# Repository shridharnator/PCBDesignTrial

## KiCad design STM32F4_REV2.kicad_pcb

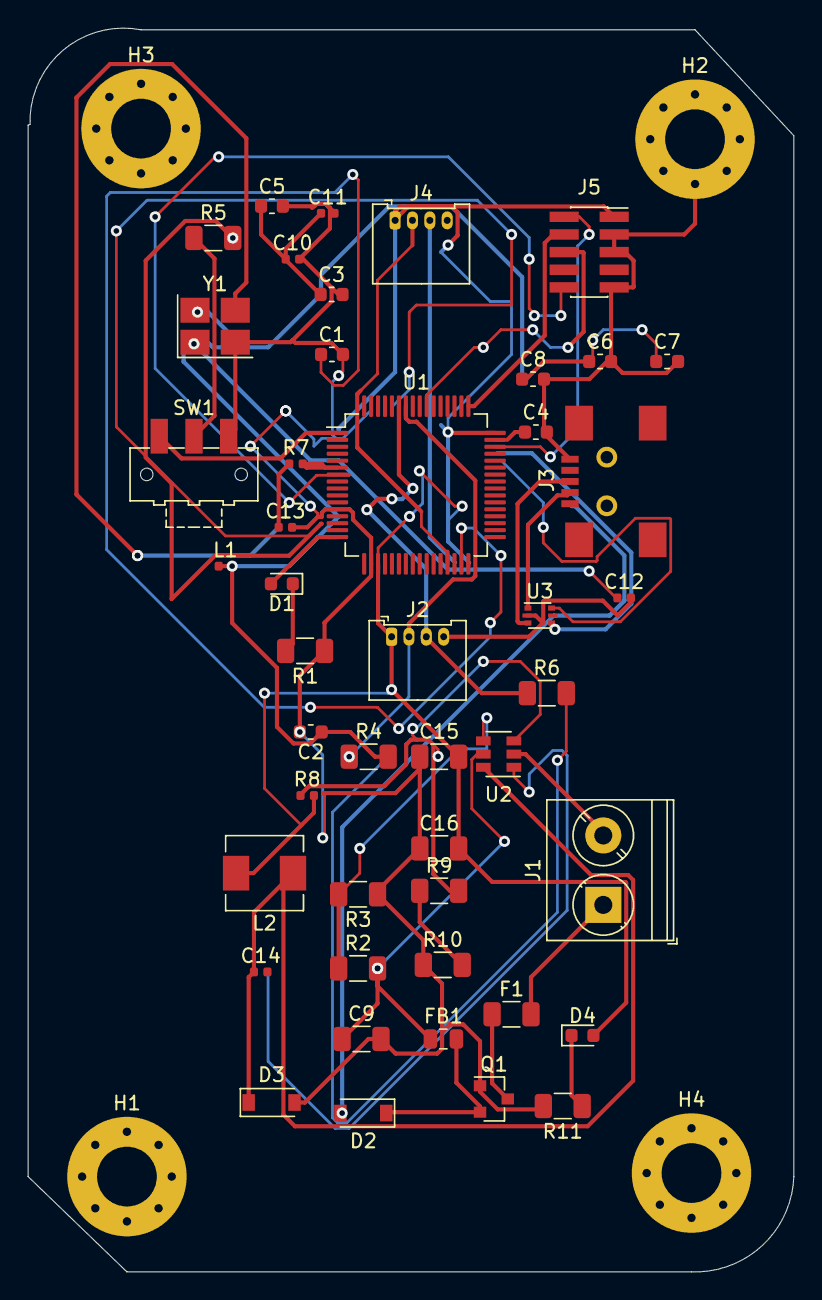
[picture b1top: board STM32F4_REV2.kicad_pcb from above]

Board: 4 copper layers, 55.1 x 89.5 mm, 50 parts (0 on the bottom side), 35 nets.

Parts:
C1, C4: 2u2; C_0603_1608Metric
C2: 4u7; C_0603_1608Metric
C3, C5, C6, C7, C8: 100n; C_0603_1608Metric
C9, C15, C16: 10u; C_1206_3216Metric
C10: 1u; C_0402_1005Metric
C11, C14: 10n; C_0402_1005Metric
C12, C13: 12p; C_0402_1005Metric
D1: Blue; LED_0603_1608Metric
D2, D3: B5819W; D_SOD-123
D4: RED; LED_0603_1608Metric
F1: 250mA; Fuse_1206_3216Metric
FB1: 600 @ 600MHz; L_0805_2012Metric
H1, H2, H3, H4: MountingHole_Pad; MountingHole_4.3mm_M4_Pad_Via
J1: Screw_Terminal_01x02; TerminalBlock_Phoenix_PT-1,5-2-5.0-H_1x02_P5.00mm_Horizontal
J2, J4: Conn_01x04; Molex_PicoBlade_53048-0410_1x04_P1.25mm_Horizontal
J3: USB_B_Micro; USB_Mini_B_Female_UX60-MB-5ST
J5: SWD; PinSocket_2x05_P1.27mm_Vertical_SMD
L1: 39n; L_0402_1005Metric
L2: 10u; L_Sunlord_MWSA0518_5.4x5.2mm
Q1: AO3401A; SOT-23
R1: 1k5; R_1206_3216Metric
R2: 100k; R_1206_3216Metric
R3: 68k; R_1206_3216Metric
R4, R6: 2k2; R_1206_3216Metric
R5: 10k; R_1206_3216Metric
R7: 47; R_0402_1005Metric
R8: 47k; R_0402_1005Metric
R9: 15k; R_1206_3216Metric
R10: 270; R_1206_3216Metric
R11: 1k; R_1206_3216Metric
SW1: SW_SPDT; SW_SPDT_CK-JS102011SAQN
U1: STM32F405RGT6; LQFP-64_10x10mm_P0.5mm
U2: MP2359DJ-LF-Z; SOT-23-6
U3: USBLC6-2P6; SOT-666
Y1: 16MHz; Crystal_SMD_3225-4Pin_3.2x2.5mm_HandSoldering

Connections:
+3.3VA: C2.1, C3.1, C5.1, C6.1, C7.1, C8.1, C10.1, C11.1, L1.1, L1.2, R4.2, R6.2, U1.13
+3V3: C15.2, C16.2, D4.2, J2.1, J4.1, J5.1, L2.2, R8.2, SW1.1, U1.1, U1.19, U1.32, U1.48, U1.64
+5V: D2.2, J3.1, U3.5
+12V: F1.2, J1.1
BOOT0: R5.2, U1.60
BUCK_BST: C14.2, U2.1
BUCK_EN: R2.1, R3.2, U2.4
BUCK_FB: R8.1, R9.2, U2.3
BUCK_IN: C9.1, FB1.1, R2.2, U2.5
BUCK_SW: C14.1, D3.1, L2.1, U2.6
GND: C1.2, C2.2, C3.2, C4.2, C5.2, C6.2, C7.2, C8.2, C9.2, C10.2, C11.2, C12.2, C13.2, C15.1, C16.1, D3.2, H1.1, H2.1, H3.1, H4.1, J1.2, J2.4, J3.5, J4.4, J5.3, J5.5, J5.9, Q1.1, R1.1, R3.1, R10.1, R11.2, SW1.3, U1.12, U1.18, U1.63, U2.2, U3.2, Y1.2, Y1.4
HSE_IN: C12.1, U1.5, Y1.1
HSE_OUT: R7.2, U1.6
I2C1_SCL: J2.2, R4.1, U1.58
I2C1_SDA: J2.3, R6.1, U1.59
LED_STATUS: D1.2, U1.16
NRST: J5.10, U1.7
unnamed: C1.1, U1.31
unnamed: C4.1, U1.47
unnamed: C13.1, R7.1, Y1.3
unnamed: D1.1, R1.2
unnamed: D2.1, FB1.2, Q1.2
unnamed: D4.1, R11.1
unnamed: F1.1, Q1.3
unnamed: R5.1, SW1.2
unnamed: R9.1, R10.2
SW0: J5.6, U1.55
SWCLK: J5.4, U1.49
SWDI0: J5.2, U1.46
UART3_RX: J4.3, U1.30
UART3_TX: J4.2, U1.29
USB_CONN_D+: J3.3, U3.3
USB_CONN_D-: J3.2, U3.1
USB_D+: U1.45, U3.4
USB_D-: U1.44, U3.6
